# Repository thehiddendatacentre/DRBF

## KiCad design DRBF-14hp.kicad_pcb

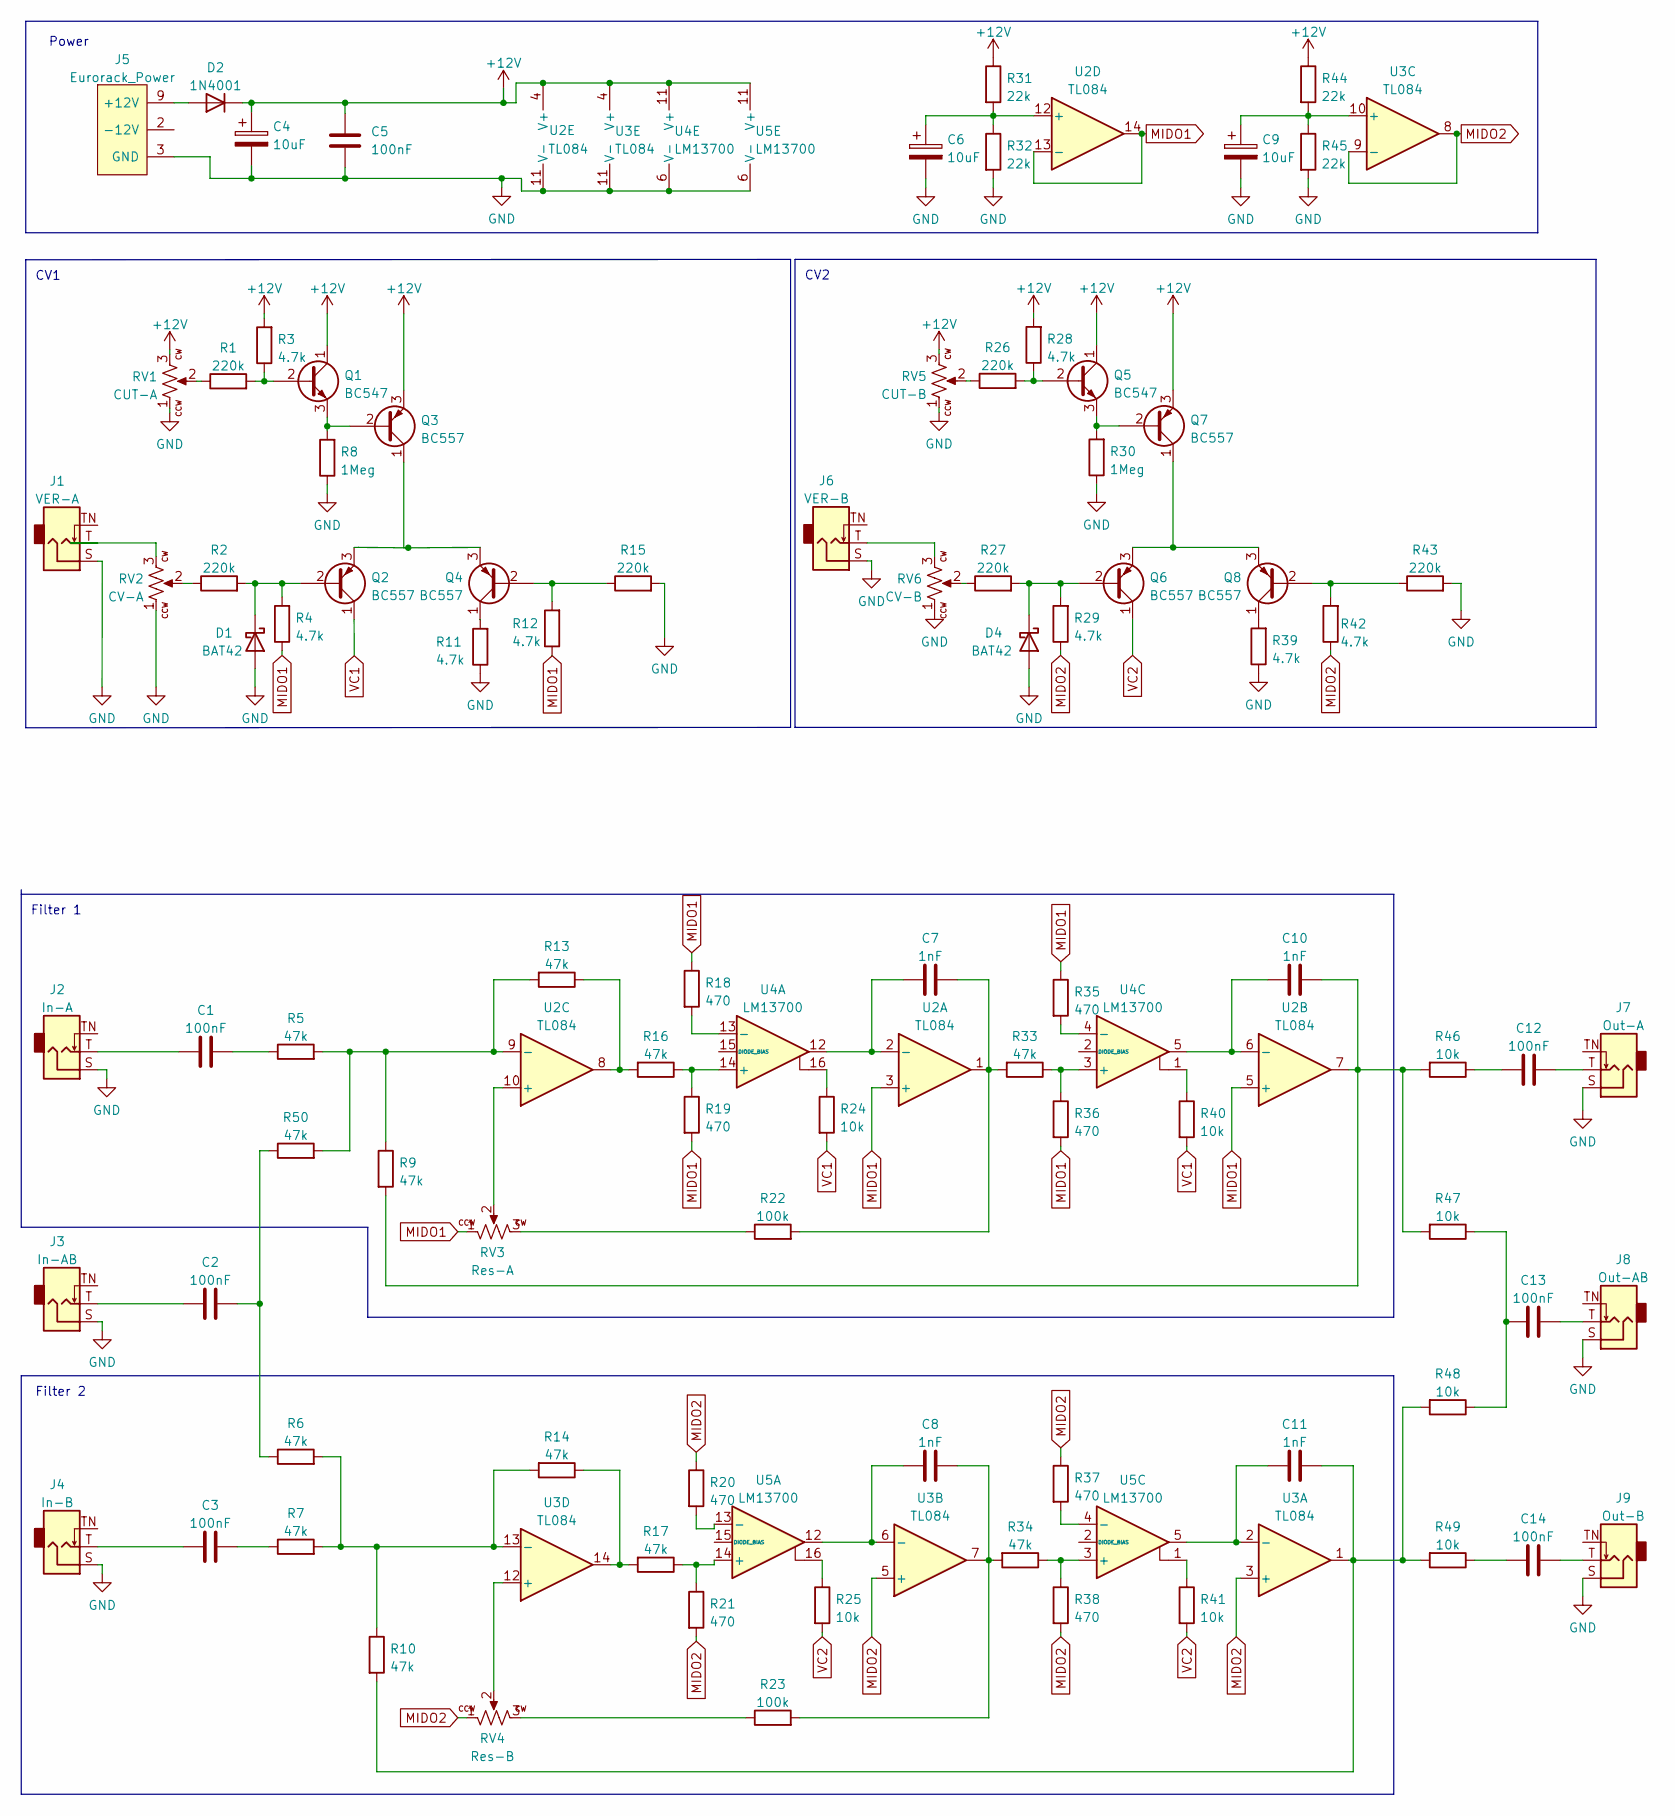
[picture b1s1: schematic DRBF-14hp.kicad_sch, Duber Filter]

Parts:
C1, C2, C3, C12, C13, C14: 100nF; C_Axial_L3.8mm_D2.6mm_P7.50mm_Horizontal
C4, C6, C9: 10uF; CP_Radial_D5.0mm_P2.50mm
C5: 100nF; C_Disc_D5.0mm_W2.5mm_P2.50mm
C7, C8, C10, C11: 1nF; C_Disc_D5.0mm_W2.5mm_P5.00mm
D1, D4: BAT42; D_DO-35_SOD27_P7.62mm_Horizontal
D2: 1N4001; D_DO-41_SOD81_P10.16mm_Horizontal
J1: VER-A; AudioJack_WQP518MA; MPN WQP-WQP518MA
J2: In-A; AudioJack_WQP518MA; MPN WQP-WQP518MA
J3: In-AB; AudioJack_WQP518MA; MPN WQP-WQP518MA
J4: In-B; AudioJack_WQP518MA; MPN WQP-WQP518MA
J5: Eurorack_Power; Eurorack_Power_2x5_Shrouded; MPN 302-S101
J6: VER-B; AudioJack_WQP518MA; MPN WQP-WQP518MA
J7: Out-A; AudioJack_WQP518MA; MPN WQP-WQP518MA
J8: Out-AB; AudioJack_WQP518MA; MPN WQP-WQP518MA
J9: Out-B; AudioJack_WQP518MA; MPN WQP-WQP518MA
Q1, Q5: BC547; TO-92_Inline
Q2, Q3, Q4, Q6, Q7, Q8: BC557; TO-92_Inline
R1, R2, R15, R26, R27, R43: 220k; R_Axial_DIN0204_L3.6mm_D1.6mm_P7.62mm_Horizontal
R3, R4, R11, R12, R28, R29, R39, R42: 4.7k; R_Axial_DIN0204_L3.6mm_D1.6mm_P7.62mm_Horizontal
R5, R6, R7, R9, R10, R13, R14, R16, R17, R33, R34, R50: 47k; R_Axial_DIN0204_L3.6mm_D1.6mm_P7.62mm_Horizontal
R8, R30: 1Meg; R_Axial_DIN0204_L3.6mm_D1.6mm_P7.62mm_Horizontal
R18, R19, R20, R21, R35, R36, R37, R38: 470; R_Axial_DIN0204_L3.6mm_D1.6mm_P7.62mm_Horizontal
R22, R23: 100k; R_Axial_DIN0204_L3.6mm_D1.6mm_P7.62mm_Horizontal
R24, R25, R40, R41, R46, R47, R48, R49: 10k; R_Axial_DIN0204_L3.6mm_D1.6mm_P7.62mm_Horizontal
R31, R32, R44, R45: 22k; R_Axial_DIN0204_L3.6mm_D1.6mm_P7.62mm_Horizontal
RV1: CUT-A; Potentiometer_Alpha_R0904N; MPN R0904N-???? L-25KQ/LWS
RV2: CV-A; Potentiometer_Alpha_R0904N; MPN R0904N-???? L-25KQ/LWS
RV3: Res-A; Potentiometer_Alpha_R0904N; MPN R0904N-???? L-25KQ/LWS
RV4: Res-B; Potentiometer_Alpha_R0904N; MPN R0904N-???? L-25KQ/LWS
RV5: CUT-B; Potentiometer_Alpha_R0904N; MPN R0904N-???? L-25KQ/LWS
RV6: CV-B; Potentiometer_Alpha_R0904N; MPN R0904N-???? L-25KQ/LWS
U2, U3: TL084; DIP-14_W7.62mm_Socket
U4, U5: LM13700; DIP-16_W7.62mm_Socket

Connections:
+12V: C4.1, C5.2, D2.1 (K), Q1.1 (C), Q3.3 (E), Q5.1 (C), Q7.3 (E), R3.2, R28.2, R31.1, R44.1, RV1.3, RV5.3, U2.4 (V+), U3.4 (V+), U4.11 (V+), U5.11 (V+)
GND: C4.2, C5.1, C6.2, C9.2, D1.2 (A), D4.2 (A), J1.S (Sleeve), J2.S (Sleeve), J3.S (Sleeve), J4.S (Sleeve), J5.3 (GND), J5.4 (GND), J5.5 (GND), J5.6 (GND), J5.7 (GND), J5.8 (GND), J6.S (Sleeve), J7.S (Sleeve), J8.S (Sleeve), J9.S (Sleeve), R8.1, R11.1, R15.2, R30.1, R32.2, R39.1, R43.2, R45.2, RV1.1, RV2.1, RV5.1, RV6.1, U2.11 (V-), U3.11 (V-), U4.6 (V-), U5.6 (V-)
MIDO1: R4.1, R12.1, R18.1, R19.2, R35.1, R36.2, RV3.1, U2.3 (+), U2.5 (+), U2.13 (-), U2.14
MIDO2: R20.1, R21.2, R29.1, R37.1, R38.2, R42.1, RV4.1, U3.3 (+), U3.5 (+), U3.8, U3.9 (-)
unnamed: C1.1, J2.T (Tip)
unnamed: C1.2, R5.1
unnamed: C2.1, J3.T (Tip)
unnamed: C2.2, R6.1, R50.1
unnamed: C3.1, J4.T (Tip)
unnamed: C3.2, R7.1
unnamed: C6.1, R31.2, R32.1, U2.12 (+)
unnamed: C7.1, U2.2 (-), U4.12
unnamed: C7.2, R22.2, R33.2, U2.1
unnamed: C8.1, U3.6 (-), U5.12
unnamed: C8.2, R23.2, R34.2, U3.7
unnamed: C9.1, R44.2, R45.1, U3.10 (+)
unnamed: C10.1, U2.6 (-), U4.5
unnamed: C10.2, R9.2, R46.2, R47.2, U2.7
unnamed: C11.1, U3.2 (-), U5.5
unnamed: C11.2, R10.2, R48.2, R49.2, U3.1
unnamed: C12.1, R46.1
unnamed: C12.2, J7.T (Tip)
unnamed: C13.1, R47.1, R48.1
unnamed: C13.2, J8.T (Tip)
unnamed: C14.1, R49.1
unnamed: C14.2, J9.T (Tip)
unnamed: D2.2 (A), J5.9 (+12V), J5.10 (+12V)
unnamed: D4.1 (K), Q6.2 (B), R27.2, R29.2
unnamed: J1.T (Tip), RV2.3
unnamed: J5.1 (-12V), J5.2 (-12V)
unnamed: J6.T (Tip), RV6.3
unnamed: Q1.2 (B), R1.2, R3.1
unnamed: Q1.3 (E), Q3.2 (B), R8.2
unnamed: Q2.3 (E), Q3.1 (C), Q4.3 (E)
unnamed: Q4.1 (C), R11.2
unnamed: Q4.2 (B), R12.2, R15.1
unnamed: Q5.2 (B), R26.2, R28.1
unnamed: Q5.3 (E), Q7.2 (B), R30.2
unnamed: Q6.3 (E), Q7.1 (C), Q8.3 (E)
unnamed: Q8.1 (C), R39.2
unnamed: Q8.2 (B), R42.2, R43.1
unnamed: R1.1, RV1.2
unnamed: R2.1, RV2.2
unnamed: D1.1 (K), Q2.2 (B), R2.2, R4.2
unnamed: R6.2, R7.2, R10.1, R14.2, U3.13 (-)
unnamed: R13.1, R16.2, U2.8
unnamed: R5.2, R9.1, R13.2, R50.2, U2.9 (-)
unnamed: R14.1, R17.2, U3.14
unnamed: R16.1, R19.1, U4.14 (+)
unnamed: R17.1, R21.1, U5.14 (+)
unnamed: R18.2, U4.13 (-)
unnamed: R20.2, U5.13 (-)
unnamed: R22.1, RV3.3
unnamed: R23.1, RV4.3
unnamed: R24.1, U4.16
unnamed: R25.1, U5.16
unnamed: R26.1, RV5.2
unnamed: R27.1, RV6.2
unnamed: R33.1, R36.1, U4.3 (+)
unnamed: R34.1, R38.1, U5.3 (+)
unnamed: R35.2, U4.4 (-)
unnamed: R37.2, U5.4 (-)
unnamed: R40.1, U4.1
unnamed: R41.1, U5.1
unnamed: RV3.2, U2.10 (+)
unnamed: RV4.2, U3.12 (+)
VC1: Q2.1 (C), R24.2, R40.2
VC2: Q6.1 (C), R25.2, R41.2

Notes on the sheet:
CV1
Filter 2
Power
Filter 1
CV2

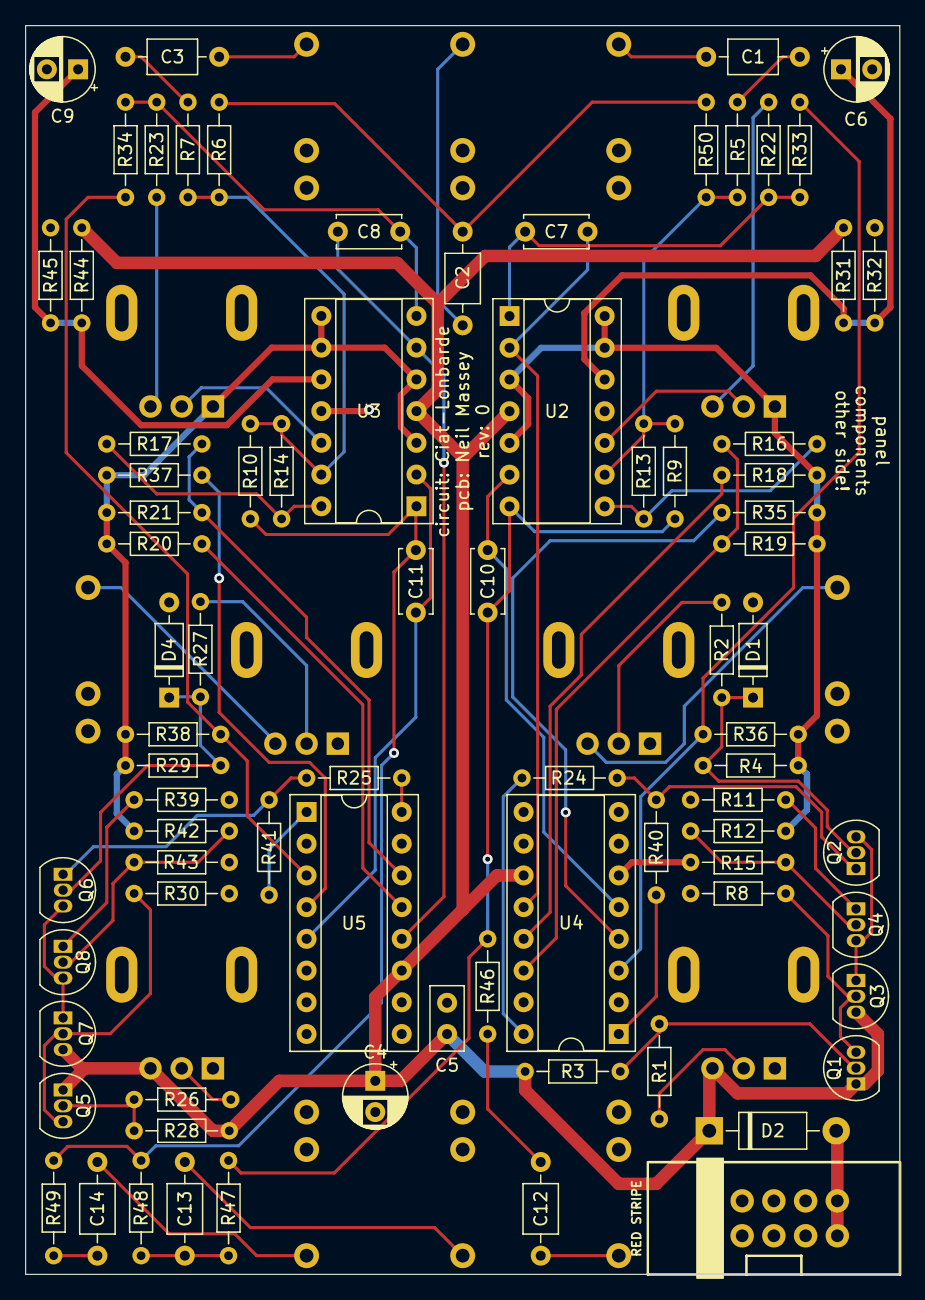
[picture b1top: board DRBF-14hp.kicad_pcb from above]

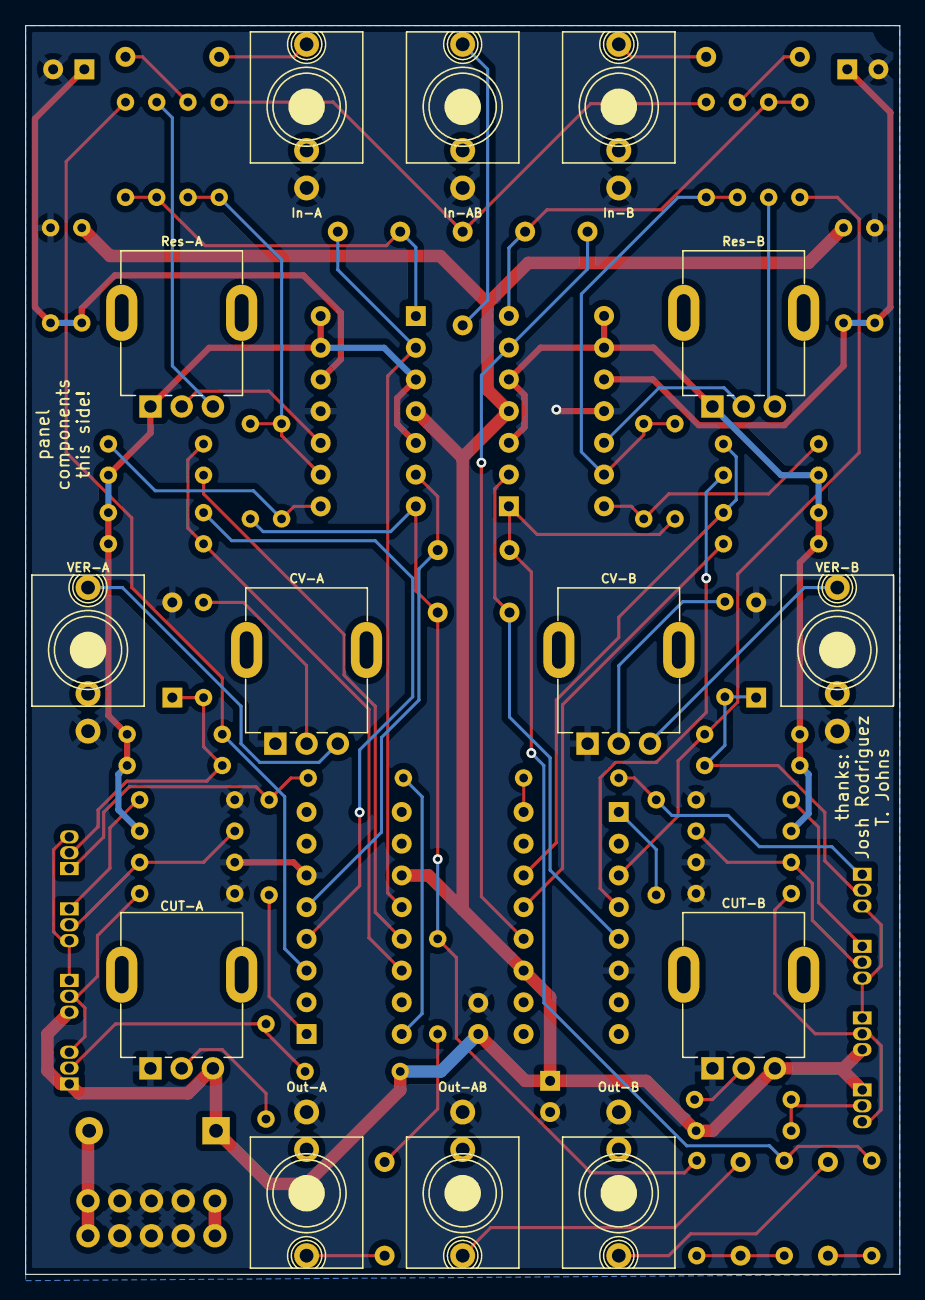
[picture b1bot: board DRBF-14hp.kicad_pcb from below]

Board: 2 copper layers, 70.0 x 100.0 mm, 94 parts (14 on the bottom side), 68 nets.

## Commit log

2023-01-28 Added LICENSE
2023-02-01 Added negative voltage protection diodes
2023-02-25 Changed to 14hp width
2023-03-03 Changed inputs to circles on panels
